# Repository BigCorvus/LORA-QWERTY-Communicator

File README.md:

# LORA-QWERTY-Communicator
A tidy, versatile and feature-packed LORA QWERTY communication device mainly based on a Blackberry Q10 keyboard, nRF52840, SX1262 and a 2.7'' Sharp Memory LCD (LS027B7DH01).
I created this because I wanted to practice a little and put some components that I had laying around to good use. The system had to have a low power consumption and outdoor usability, hence the component choices. The SX1262 draws 4,6mA in RX mode and the nRF52 can poll the keyboard while also drawing little power. Without optimizing anything I got 12mA. This can be further reduced by turning off some sensors. The unit can monitor its own power consumption and battery charge status via a BQ27441 Lithium Fuel Gauge.  

Some words about the memory LCDs: I got fake ones from Ali and only one out of three works properly! One consumes 20mA instead of ~400µA and one had some dead pixels after some days of usage (seen on the pictures). They are not that much cheaper (~25 vs ca 32$), so avoid them and only get genuine SHARP displays from digikey or so.  
There is a passive piezo buzzer (9032 type) and a vibration motor ("10x4mm" look on Aliexpress) for notification purposes. A BME280 can be soldered for altimeter functionality. A DS3231M RTC is supposed to keep time (the wires on the images are for optional backup battery connection). A MPU9250 9-DOF IMU was included to act as a tilt-compensated compass or for air mouse functionality. A GD25Q16CE QSPI flash (apparently optional, not required by the bootloader, works with mass storage TinyUSB test sketch) and an µSD card slot for storage of for example chat history or sensor values. An optional GPS module can be connected to the exposed connector at the top of the device. I used a BN220 which fits into the enclosure if you use an appropriate LiPo cell. All I2C sensor are on one I2C bus and are optional. They do not need to be populated. Time and altitude can just as well be fetched via GPS. The connector for the Q10 keyboard is a Hirose BM14B(0.8)-24DS-0.4V(53)     

The repository contains the EAGLE PCB design files, gerber, pick and place and BOM files, Solidworks design files and .STL for a perfectly fitting enclosure and an Arduino test sketch to test most of the system components. The enclosure lacks inserts for the pushbutton and slide swith. This I will add in the future. You require 4 2mmx10mm plastic screws to hold it together. The resulting device has a thickness of only about 13,5mm.  
While the hardware is confirmed working (only one minor bug had to be fixed in the prototype - conflicting I2C addresses), the firmware part is very raw and has yet to be developed. Unfortunately I lack time desperately for such hobby things at the moment. What I had in mind for this device is mainly something like an encrypted "apocalypse" LORA communicator, maybe even based on Meshtastic. It can also communicate with other BLE devices and acquire, log and share sensor data or act as a USB or BLE HID keyboard. The test firmware is based on the Adafruit nRF52 core v1.0.0. In order for the device to be programmable via the Arduino IDE, the Feather nRF52840 Express bootloader has to be flashed, which I usually do via a J-Link and the Arduino IDE ("Burn Bootloader"). The bootloader can be activated at any time double-pulling the reset pin low. In a future revision there should also be reset button for that purpose, now there is at least a test point. The variant files for the Feather nRF52840 express need to be modified as well before programming the board. They are provided with the test sketch together with a readme.  

UPDATE: Sam Altman and I created a nicely functioning Meshtastic port for this devices. The project is available as a zipped archive and as prebuilt-binaries.

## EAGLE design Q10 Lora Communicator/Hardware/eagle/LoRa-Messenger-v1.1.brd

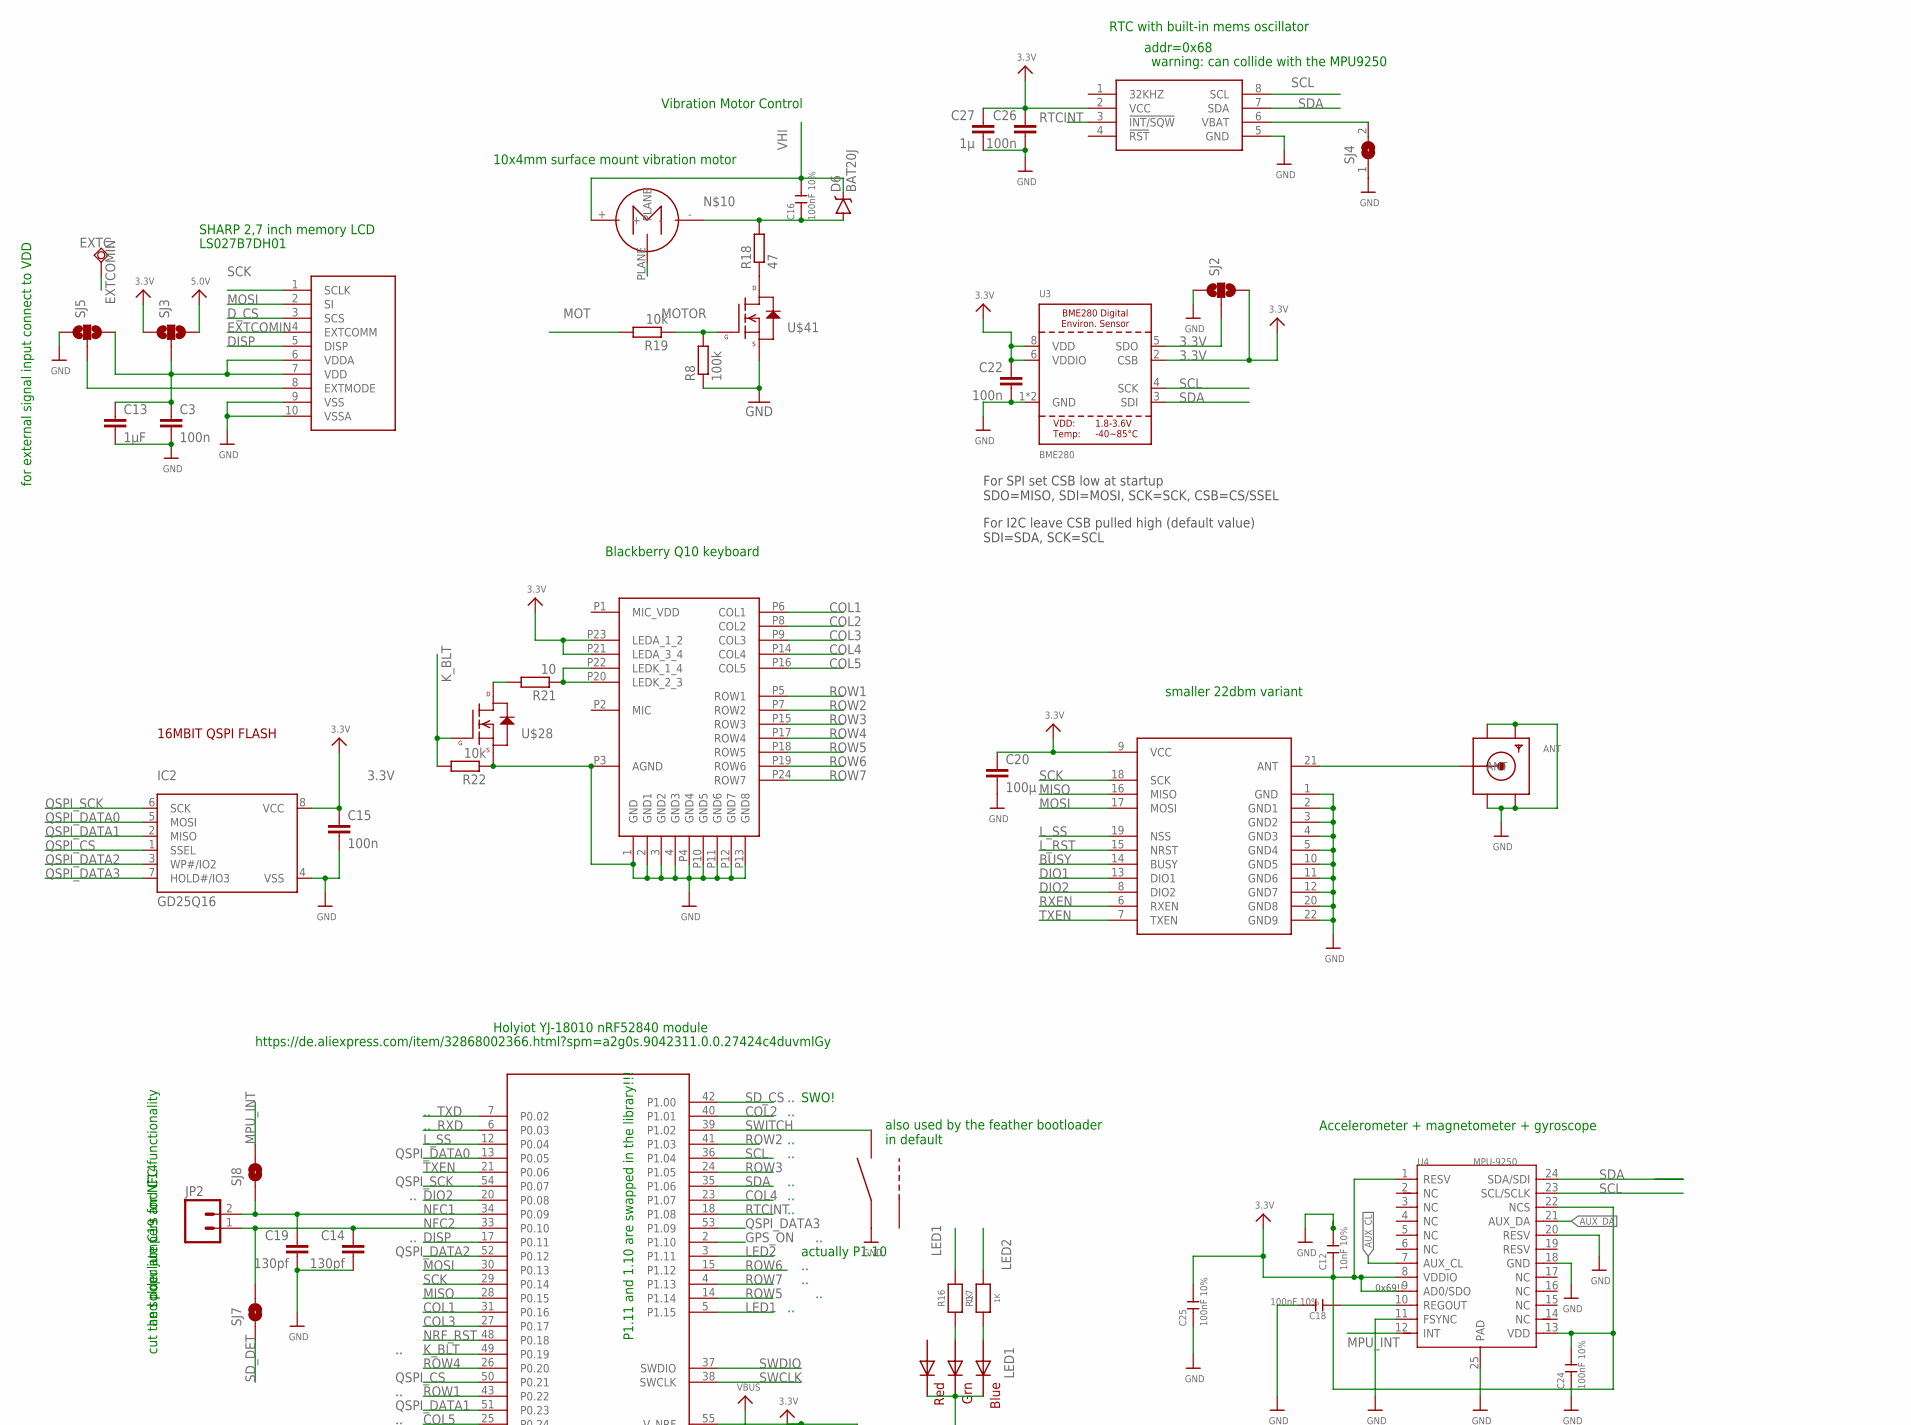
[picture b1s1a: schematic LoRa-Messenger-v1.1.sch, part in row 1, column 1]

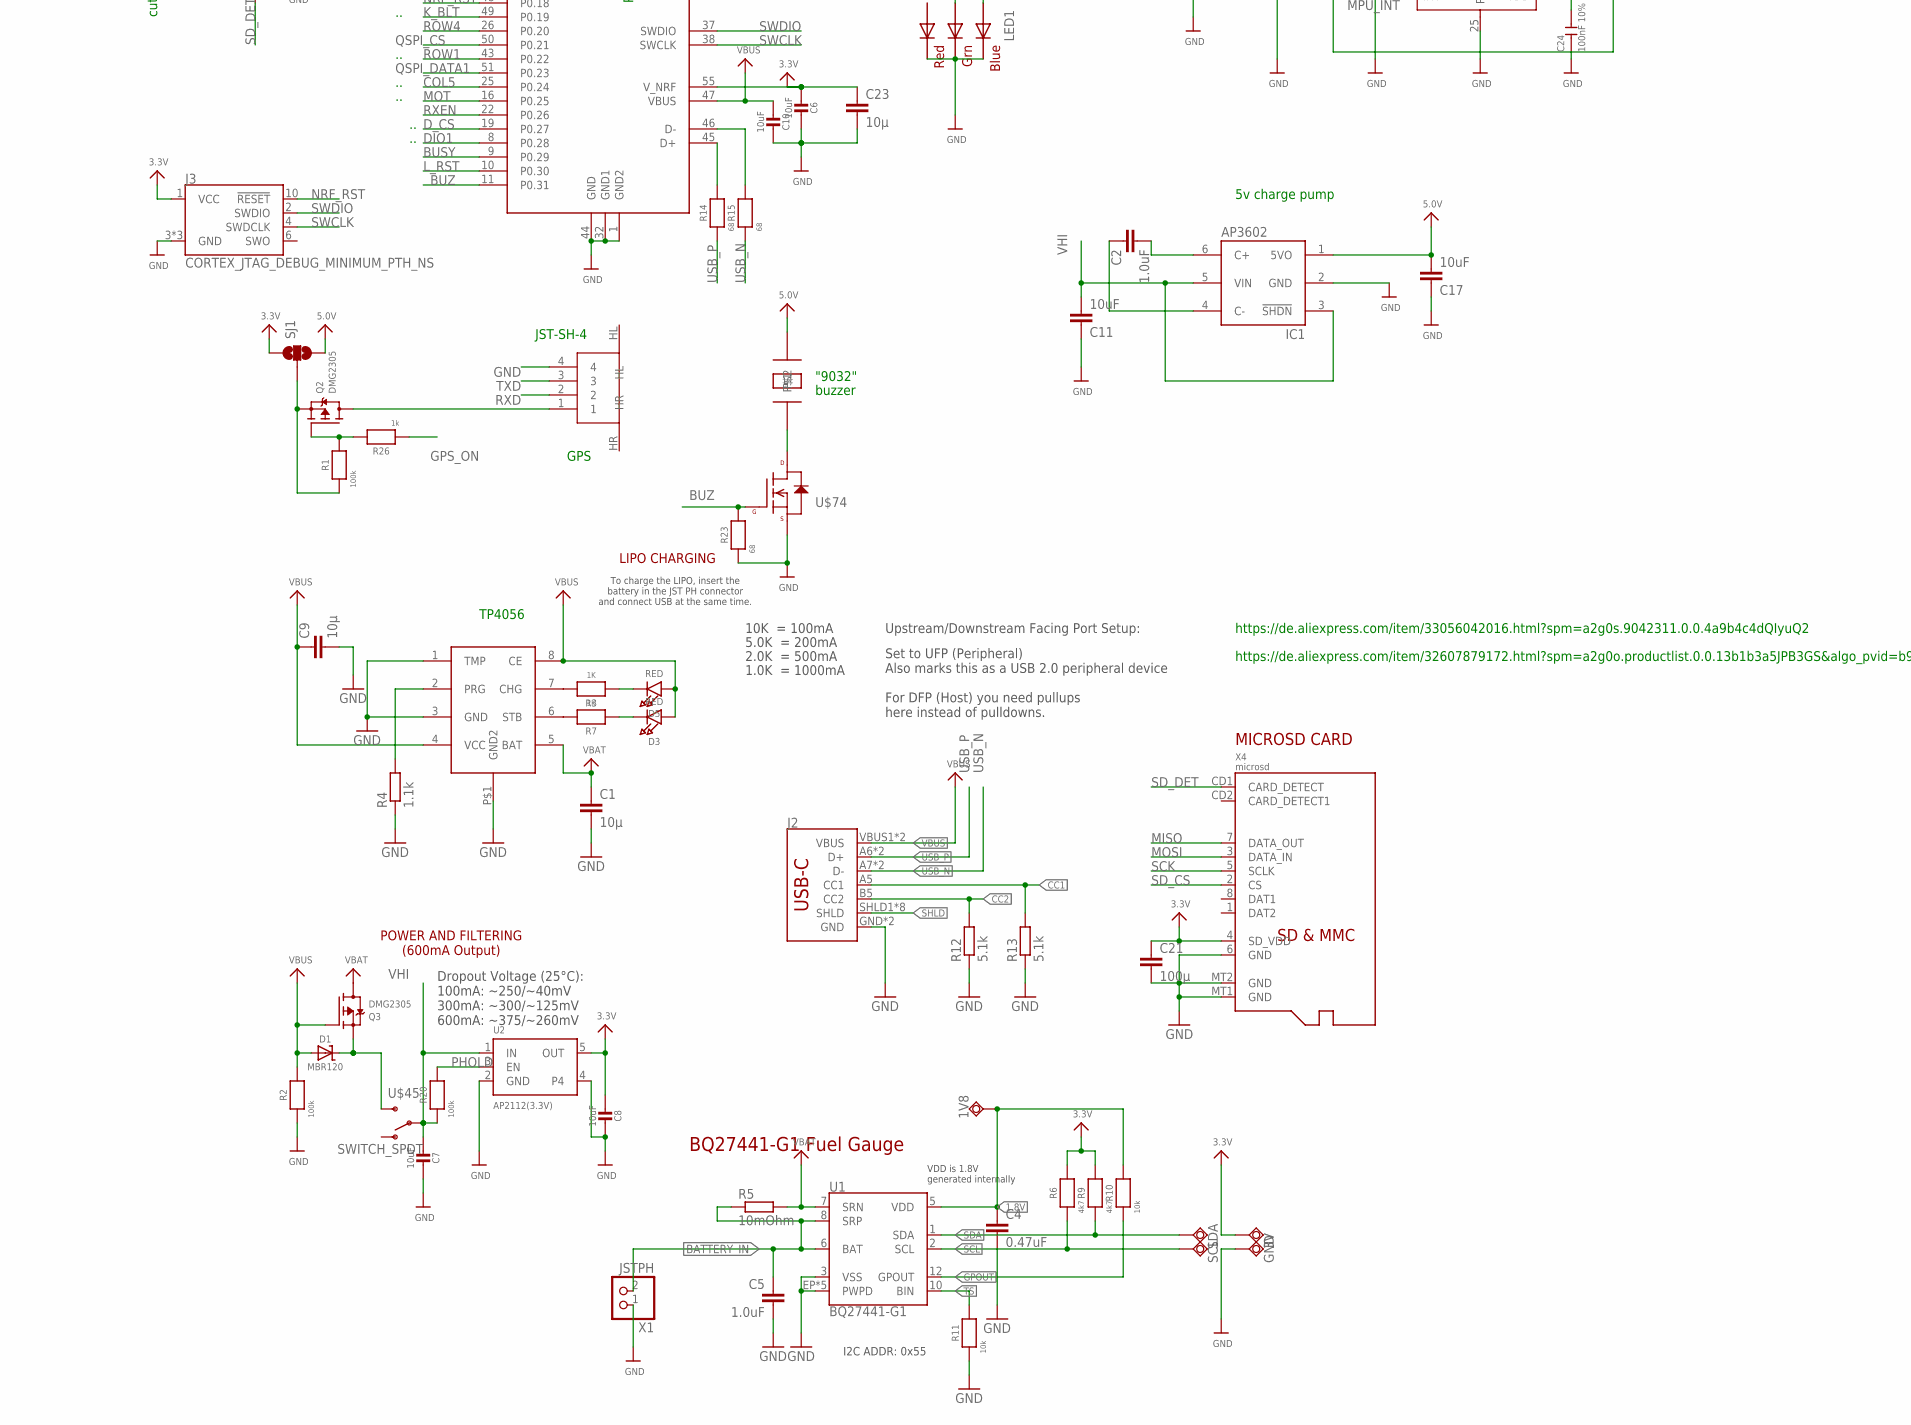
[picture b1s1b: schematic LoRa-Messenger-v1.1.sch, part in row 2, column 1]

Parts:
1V8, 3V: TPSQTP13R; TP13R
ANT: SMACONNECTOR_EDGE; SMA_EDGELAUNCH
C1, C9, C23: 10µ; C0805
C2, C5: 1.0uF; 0603-CAP
C3, C15: 100n; C0402
C4: 0.47uF; 0603-CAP
C6, C7, C8, C10: 10uF; 0805-NO
C11, C17: 10uF; 0603-CAP
C12: 10nF 10%; C0603
C13: 1µF; C0402
C14, C19: 130pf; 0603-CAP
C16, C18, C24, C25: 100nF 10%; C0603
C20, C21: 100µ; C1206
C22, C26: 100n; 0603-CAP
C27: 1µ; 0603-CAP
D1: MBR120; SOD-123
D3, D5: RED; CHIPLED_0805_NOOUTLINE
D6: BAT20J; SOD-323
DWN2: LS12T2
EXTC.: TPSQTP13R; TP13R
GND: TPSQTP13R; TP13R
IC1: AP3602; SOT23-6
IC2: GD25Q16; USON8
J2: USB_C16PIN; USB-C-16P
J3: CORTEX_JTAG_DEBUG_MINIMUM_PTH_NS; 2X5-PTH-1.27MM-NO_SILK
JP2: M02PTH; 1X02
LED1: RGBLED5050
Q2, Q3: DMG2305; SOT23-R
R1, R2, R20: 100k; 0603-NO
R3, R7, R16, R17: 1K; 0603-NO
R4: 1.1k; R0603
R5: 10mOhm; R0805
R6, R9: 4k7; 0603-NO
R8: 100k; R0603
R10, R11: 10k; 0603-NO
R12, R13: 5.1k; R0603
R14, R15, R23: 68; 0603-NO
R18: 47; R0603
R19, R22: 10k; R0603
R21: 10; R0603
R26: 1k; 0603-NO
SCL: TPSQTP13R; TP13R
SDA: TPSQTP13R; TP13R
SJ1, SJ2, SJ3, SJ5: SOLDERJUMPER_2WAY-OLDS; SJ_3
SJ4: SJ
SJ7, SJ8: SOLDERJUMPERTRACE; SJ_2S-TRACE
U1: BQ27441-G1; PDSO-N12
U2: AP2112(3.3V); SOT23-5
U3: BME280
U4: MPU-9250; LEAD-QFN24
U$2: BUZZER
U$7: Q10KEYBOARD
U$10: AYF531035_SHARP_MEM_DISP; AYF531035_Y5BW
U$14: NRF52840; NRF52840MOD
U$17: JST-SH-3
U$28, U$41, U$74: N-CHANNEL-MOSFET-BSS138; SOT23-3
U$36: SX1292-EBYTE; SX1262_EBYTE
U$45: SWITCH_SPDT; KPS-1290
U$46: VIBRO
U$47: TP4056BETTER_TP4056; TP4056BETTER_SO-08
U$69: DS3231M; SO8
X1: JSTPH; JSTPH2
X4: microsd; MICROSD

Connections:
1.8V: 1V8.TP, C4.1, R10.2, U1.5 (VDD)
3.3V: 3V.TP, C6.2, C8.2, C12.1, C15.1, C20.1, C21.1, C22.1, C23.1, C24.2, C25.2, C26.1, C27.1, IC2.8 (VCC), J3.1 (VCC), R6.2, R9.2, SJ1.1, SJ2.3, SJ3.1, U2.5 (OUT), U3.2 (CSB), U3.6 (VDDIO), U3.8 (VDD), U4.1 (RESV), U4.8 (VDDIO), U4.9 (AD0/SDO), U4.13 (VDD), U4.22 (NCS), U$7.P21 (LEDA_3_4), U$7.P23 (LEDA_1_2), U$14.55 (V_NRF), U$36.9 (VCC), U$69.2 (VCC), X4.4 (SD_VDD)
5.0V: C17.2, IC1.1 (5VO), SJ1.3, SJ3.3, U$2.P$1
AUX_CL: U4.7 (AUX_CL)
AUX_DA: U4.21 (AUX_DA)
BATTERY_IN: C5.1, R5.1, U1.6 (BAT), U1.8 (SRP), X1.2
BUSY: U$14.9 (P0.29), U$36.14 (BUSY)
BUZ: R23.2, U$14.11 (P0.31), U$74.1 (G)
CC1: J2.A5 (CC1), R13.2
CC2: J2.B5 (CC2), R12.2
COL1: U$7.P6 (COL1), U$14.31 (P0.16)
COL2: U$7.P8 (COL2), U$14.40 (P1.01)
COL3: U$7.P9 (COL3), U$14.27 (P0.17)
COL4: U$7.P14 (COL4), U$14.23 (P1.07)
COL5: U$7.P16 (COL5), U$14.25 (P0.24)
DIO1: U$14.8 (P0.28), U$36.13 (DIO1)
DIO2: U$14.20 (P0.08), U$36.8 (DIO2)
DISP: U$10.5 (DISP), U$14.17 (P0.11)
D_CS: U$10.3 (SCS), U$14.19 (P0.27)
EXTCOMIN: EXTC..TP, U$10.4 (EXTCOMM)
GND: ANT.GND@1 (GND4), ANT.GND@2 (GND3), ANT.GND@3 (GND2), ANT.GND@4 (GND1), C1.2, C3.2, C4.2, C5.2, C6.1, C7.1, C8.1, C9.2, C10.1, C11.1, C12.2, C13.2, C14.2, C15.2, C17.1, C18.2, C19.2, C20.2, C21.2, C22.2, C23.2, C24.1, C25.1, C26.2, C27.2, DWN2.2, GND.TP, IC1.2 (GND), IC2.4 (VSS), J2.GND, J2.GND2 (GND), J3.3 (GND), J3.5 (GND), J3.9 (GND), LED1.4 (BLUE_C), LED1.5 (RED_C), LED1.6 (GREEN_C), R2.1, R4.1, R8.1, R11.1, R12.1, R13.1, R22.1, R23.1, SJ2.1, SJ4.1, SJ5.1, U1.3 (VSS), U1.EP (PWPD), U1.EP1 (PWPD), U1.EP2 (PWPD), U1.EP3 (PWPD), U1.EP4 (PWPD), U2.2 (GND), U2.4, U3.1 (GND), U3.7 (GND), U4.11 (FSYNC), U4.18 (GND), U4.20 (RESV), U4.25 (PAD), U$7.1 (GND), U$7.2 (GND1), U$7.3 (GND2), U$7.4 (GND3), U$7.P3 (AGND), U$7.P4 (GND4), U$7.P10 (GND5), U$7.P11 (GND6), U$7.P12 (GND7), U$7.P13 (GND8), U$10.9 (VSS), U$10.10 (VSSA), U$14.1 (GND2), U$14.32 (GND1), U$14.44 (GND), U$17.4, U$28.2 (S), U$36.1 (GND), U$36.2 (GND1), U$36.3 (GND2), U$36.4 (GND3), U$36.5 (GND4), U$36.10 (GND5), U$36.11 (GND6), U$36.12 (GND7), U$36.20 (GND8), U$36.22 (GND9), U$41.2 (S), U$47.1 (TMP), U$47.3 (GND), U$47.P$1 (GND2), U$69.5 (GND), U$74.2 (S), X1.1, X4.6 (GND), X4.MT1 (GND), X4.MT2 (GND)
GPOUT: R10.1, U1.12 (GPOUT)
GPS_ON: R26.1, U$14.2 (P1.10)
K_BLT: R22.2, U$14.49 (P0.19), U$28.1 (G)
LED1: R16.2, U$14.5 (P1.15)
LED2: R17.2, U$14.3 (P1.11)
L_RST: U$14.10 (P0.30), U$36.15 (NRST)
L_SS: U$14.12 (P0.04), U$36.19 (NSS)
MISO: U$14.28 (P0.15), U$36.16 (MISO), X4.7 (DATA_OUT)
MOSI: U$10.2 (SI), U$14.30 (P0.13), U$36.17 (MOSI), X4.3 (DATA_IN)
MOT: R19.2, U$14.16 (P0.25)
MOTOR: R8.2, R19.1, U$41.1 (G)
MPU_INT: SJ8.2, U4.12 (INT)
unnamed: R3.2, U$47.7 (CHG)
unnamed: C2.2, IC1.6 (C+)
unnamed: C2.1, IC1.4 (C-)
unnamed: D1.C, Q3.2 (S), U$45.S
unnamed: Q2.1 (G), R1.2, R26.2
unnamed: R14.2, U$14.45 (D+)
unnamed: R15.2, U$14.46 (D-)
unnamed: R7.2, U$47.6 (STB)
unnamed: R18.1, U$41.3 (D)
unnamed: C16.1, D6.A, R18.2, U$46.-
unnamed: D5.C, R3.1
unnamed: D3.C, R7.1
unnamed: LED1.1 (GREEN_A), R16.1
unnamed: Q2.3 (D), U$17.1
unnamed: R21.1, U$7.P20 (LEDK_2_3), U$7.P22 (LEDK_1_4)
unnamed: Q2.2 (S), R1.1, SJ1.2
unnamed: R21.2, U$28.3 (D)
unnamed: ANT.P (ANT), U$36.21 (ANT)
unnamed: LED1.3 (BLUE_A), R17.1
unnamed: SJ2.2, U3.5 (SDO)
unnamed: U$2.P$2, U$74.3 (D)
unnamed: C18.1, U4.10 (REGOUT)
unnamed: SJ4.2, U$69.6 (VBAT)
unnamed: C3.1, C13.1, SJ3.2, SJ5.3, U$10.6 (VDDA), U$10.7 (VDD)
unnamed: SJ5.2, U$10.8 (EXTMODE)
NFC1: C19.1, JP2.2, SJ8.1, U$14.34 (P0.09)
NFC2: C14.1, JP2.1, SJ7.2, U$14.33 (P0.10)
NRF_RST: J3.10 (!RESET), U$14.48 (P0.18)
PHOLD: R20.2, U2.3 (EN)
PLANE: U$46.PLANE
PRG: R4.2, U$47.2 (PRG)
QSPI_CS: IC2.1 (SSEL), U$14.50 (P0.21)
QSPI_DATA0: IC2.5 (MOSI), U$14.13 (P0.05)
QSPI_DATA1: IC2.2 (MISO), U$14.51 (P0.23)
QSPI_DATA2: IC2.3 (WP#/IO2), U$14.52 (P0.12)
QSPI_DATA3: IC2.7 (HOLD#/IO3), U$14.53 (P1.09)
QSPI_SCK: IC2.6 (SCK), U$14.54 (P0.07)
ROW1: U$7.P5 (ROW1), U$14.43 (P0.22)
ROW2: U$7.P7 (ROW2), U$14.41 (P1.03)
ROW3: U$7.P15 (ROW3), U$14.24 (P1.05)
ROW4: U$7.P17 (ROW4), U$14.26 (P0.20)
ROW5: U$7.P18 (ROW5), U$14.14 (P1.14)
ROW6: U$7.P19 (ROW6), U$14.15 (P1.12)
ROW7: U$7.P24 (ROW7), U$14.4 (P1.13)
RTCINT: U$14.18 (P1.08), U$69.3 (!INT/SQW)
RXD: U$14.6 (P0.03), U$17.2
RXEN: U$14.22 (P0.26), U$36.6 (RXEN)
SCK: U$10.1 (SCLK), U$14.29 (P0.14), U$36.18 (SCK), X4.5 (SCLK)
SCL: R6.1, SCL.TP, U1.2 (SCL), U3.4 (SCK), U4.23 (SCL/SCLK), U$14.36 (P1.04), U$69.8 (SCL)
SDA: R9.1, SDA.TP, U1.1 (SDA), U3.3 (SDI), U4.24 (SDA/SDI), U$14.35 (P1.06), U$69.7 (SDA)
SD_CS: U$14.42 (P1.00), X4.2 (CS)
SD_DET: SJ7.1, X4.CD1 (CARD_DETECT)
SHLD: J2.SHLD1 (SHLD), J2.SHLD2 (SHLD), J2.SHLD3 (SHLD), J2.SHLD4 (SHLD), J2.SHLD5 (SHLD), J2.SHLD6 (SHLD), J2.SHLD7 (SHLD), J2.SHLD8 (SHLD)
SWCLK: J3.4 (SWDCLK), U$14.38 (SWCLK)
SWDIO: J3.2 (SWDIO), U$14.37 (SWDIO)
SWITCH: DWN2.1, U$14.39 (P1.02)
TS: R11.2, U1.10 (BIN)
TXD: U$14.7 (P0.02), U$17.3
TXEN: U$14.21 (P0.06), U$36.7 (TXEN)
USB_N: J2.A7 (D-), J2.B7 (D-), R15.1
USB_P: J2.A6 (D+), J2.B6 (D+), R14.1
VBAT: C1.1, Q3.3 (D), R5.2, U1.7 (SRN), U$47.5 (BAT)
VBUS: C9.1, C10.2, D1.A, D3.A, D5.A, J2.VBUS1 (VBUS), J2.VBUS2 (VBUS), Q3.1 (G), R2.2, U$14.47 (VBUS), U$47.4 (VCC), U$47.8 (CE)
VHI: C7.2, C11.2, C16.2, D6.C, IC1.3 (!SHDN), IC1.5 (VIN), R20.1, U2.1 (IN), U$45.P, U$46.+

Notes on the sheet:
POWER AND FILTERING (600mA Output)
Dropout Voltage (25°C): 100mA: ~250/~40mV 300mA: ~300/~125mV 600mA: ~375/~260mV
10K = 100mA
5.0K = 200mA
2.0K = 500mA
1.0K = 1000mA
LIPO CHARGING
To charge the LIPO, insert the battery in the JST PH connector and connect USB at the same time.
BQ27441-G1 Fuel Gauge
VDD is 1.8V generated internally
I2C ADDR: 0x55
Holyiot YJ-18010 nRF52840 module
P1.11 and 1.10 are swapped in the library!!!
GPS
MICROSD CARD
Set to UFP (Peripheral) Also marks this as a USB 2.0 peripheral device For DFP (Host) you need pullups here instead of pulldowns.
Upstream/Downstream Facing Port Setup:
JST-SH-4
TP4056
smaller 22dbm variant
also used by the feather bootloader in default
For SPI set CSB low at startup SDO=MISO, SDI=MOSI, SCK=SCK, CSB=CS/SSEL
For I2C leave CSB pulled high (default value) SDI=SDA, SCK=SCL
actually P1.10
https://de.aliexpress.com/item/33056042016.html?spm=a2g0s.9042311.0.0.4a9b4c4dQIyuQ2
https://de.aliexpress.com/item/32868002366.html?spm=a2g0s.9042311.0.0.27424c4duvmlGy
https://de.aliexpress.com/item/32607879172.html?spm=a2g0o.productlist.0.0.13b1b3a5JPB3GS&algo_pvid=b9191f80-57f7-4ba1-a376-d5b7fd01a70f&algo_expid=b9191f80-57f7-4ba1-a376-d5b7fd01a70f-25&btsid=0ab50f4915950751178702682eb47a&ws_ab_test=searchweb0_0,searchweb201602_,searchweb201603_
16MBIT QSPI FLASH
for external signal input connect to VDD
Vibration Motor Control
0x69!!
Accelerometer + magnetometer + gyroscope
RTC with built-in mems oscillator
SWO!
cut the solder jumpers for NFC functionality
and populate C19 and C14
Blackberry Q10 keyboard
SHARP 2,7 inch memory LCD
addr=0x68
5v charge pump

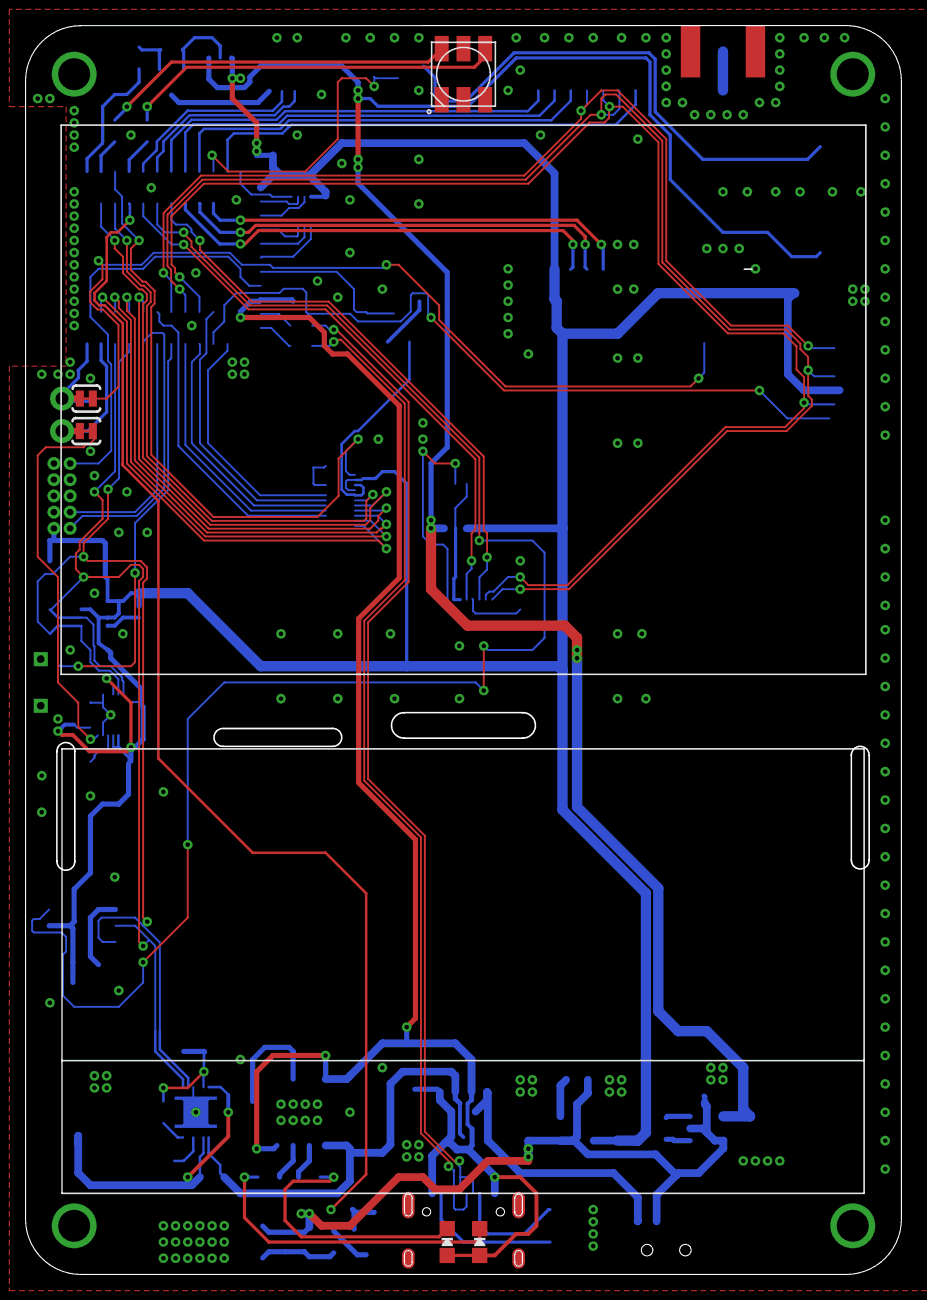
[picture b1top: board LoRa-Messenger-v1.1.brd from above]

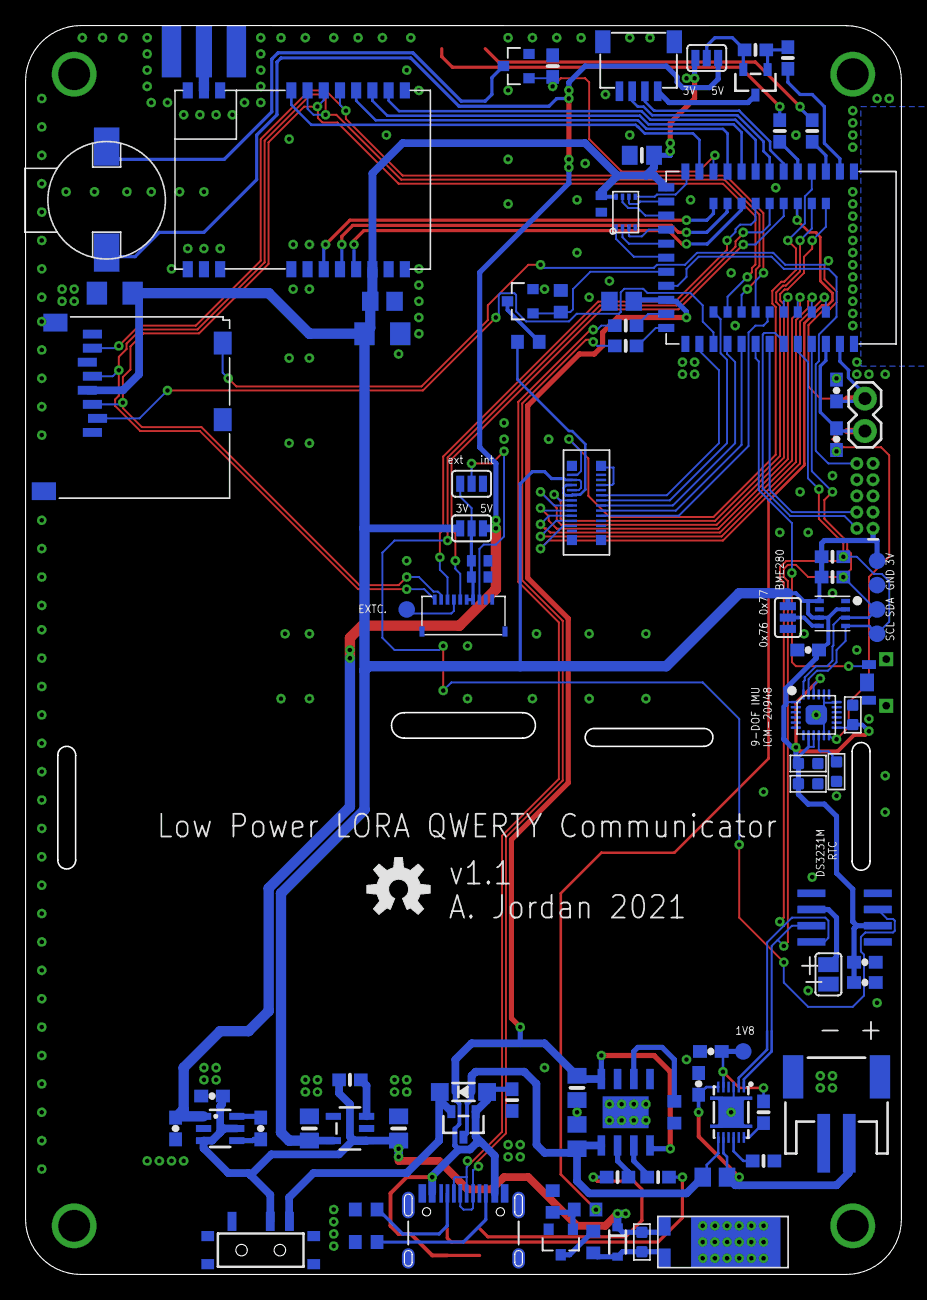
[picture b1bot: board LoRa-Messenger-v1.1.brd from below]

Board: 2 copper layers, 68.6 x 97.8 mm, 98 parts (91 on the bottom side), 94 nets.

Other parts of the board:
U$77: OSHW-LOGO-M

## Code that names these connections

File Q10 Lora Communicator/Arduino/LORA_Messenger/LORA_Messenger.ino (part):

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//#define SPI_MOSI         13
//#define SPI_SCK          14
//Q10 keyboard defines
#define col1    16
#define col2    33
#define col3    17
#define col4    39
#define col5    24

#define row1    22
#define row2    35
#define row3    37
#define row4    20
#define row5    46
#define row6    44
#define row7    45
//PIN defines
#define IMU_INT       9
#define RTC_INT       40
#define PIN_BUZZER    31
#define GPS_ON        43 //LOW means on
#define MOT           25 //HIGH means ON
#define K_BLT         19 //HIGH means ON
#define DISP_CS       27
#define DISP_DISP     11
#define BTN           34 
#define SD_CS         32
#define SD_DET        10

#define DIO1 (28)
#define DIO2 (8)
#define TXEN (6)
#define RXEN (26)
#define L_SS (4)
#define BUSY (29)
#define L_RST (30)

//-------------------menue variables-------------------
//in order to add a new app you have to:
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
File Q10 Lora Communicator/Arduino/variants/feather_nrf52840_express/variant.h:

 /*
  Copyright (c) 2014-2015 Arduino LLC.  All right reserved.
  Copyright (c) 2016 Sandeep Mistry All right reserved.
  Copyright (c) 2018, Adafruit Industries (adafruit.com)

  This library is free software; you can redistribute it and/or
  modify it under the terms of the GNU Lesser General Public
  License as published by the Free Software Foundation; either
  version 2.1 of the License, or (at your option) any later version.
  This library is distributed in the hope that it will be useful,
  but WITHOUT ANY WARRANTY; without even the implied warranty of
  MERCHANTABILITY or FITNESS FOR A PARTICULAR PURPOSE.
  See the GNU Lesser General Public License for more details.
  You should have received a copy of the GNU Lesser General Public
  License along with this library; if not, write to the Free Software
  Foundation, Inc., 51 Franklin St, Fifth Floor, Boston, MA  02110-1301  USA
*/

#ifndef _VARIANT_FEATHER52840_
#define _VARIANT_FEATHER52840_

/** Master clock frequency */
#define VARIANT_MCK       (64000000ul)

#define USE_LFXO      // Board uses 32khz crystal for LF
// define USE_LFRC    // Board uses RC for LF

/*----------------------------------------------------------------------------
 *        Headers
 *----------------------------------------------------------------------------*/

#include "WVariant.h"

#ifdef __cplusplus
extern "C"
{
#endif // __cplusplus


// Number of pins defined in PinDescription array
#define PINS_COUNT           (48)
#define NUM_DIGITAL_PINS     (48)
#define NUM_ANALOG_INPUTS    (6) // A6 is used for battery, A7 is analog reference
#define NUM_ANALOG_OUTPUTS   (0)

// LEDs
#define PIN_LED1             (42)
#define PIN_LED2             (47)
#define PIN_NEOPIXEL         (8)
#define NEOPIXEL_NUM         1

#define LED_BUILTIN          PIN_LED1
#define LED_CONN             PIN_LED2

#define LED_RED              PIN_LED1
#define LED_BLUE             PIN_LED2

#define LED_STATE_ON         1         // State when LED is litted

/*
 * Buttons
 */
#define PIN_BUTTON1          (34)

/*
 * Analog pins
 */
#define PIN_A0               (14)
#define PIN_A1               (15)
#define PIN_A2               (16)
#define PIN_A3               (17)
#define PIN_A4               (18)
#define PIN_A5               (19)
#define PIN_A6               (20)
#define PIN_A7               (21)

static const uint8_t A0  = PIN_A0 ;
static const uint8_t A1  = PIN_A1 ;
static const uint8_t A2  = PIN_A2 ;
static const uint8_t A3  = PIN_A3 ;
static const uint8_t A4  = PIN_A4 ;
static const uint8_t A5  = PIN_A5 ;
static const uint8_t A6  = PIN_A6 ;
static const uint8_t A7  = PIN_A7 ;
#define ADC_RESOLUTION    14

// Other pins
#define PIN_AREF           PIN_A7
#define PIN_VBAT           PIN_A6
#define PIN_NFC1           (9)
#define PIN_NFC2           (10)

static const uint8_t AREF = PIN_AREF;

/*
 * Serial interfaces
 */
#define PIN_SERIAL1_RX       (3)
#define PIN_SERIAL1_TX       (2)

/*
 * SPI Interfaces
 */
#define SPI_INTERFACES_COUNT 1

#define PIN_SPI_MISO         (15)
#define PIN_SPI_MOSI         (13)
#define PIN_SPI_SCK          (14)

static const uint8_t SS   = (27);
static const uint8_t MOSI = PIN_SPI_MOSI ;
static const uint8_t MISO = PIN_SPI_MISO ;
static const uint8_t SCK  = PIN_SPI_SCK ;

/*
 * Wire Interfaces
 */
#define WIRE_INTERFACES_COUNT 1

#define PIN_WIRE_SDA         (38)
#define PIN_WIRE_SCL         (36)

// QSPI Pins
#define PIN_QSPI_SCK         7
#define PIN_QSPI_CS          21
#define PIN_QSPI_IO0         5
#define PIN_QSPI_IO1         23
#define PIN_QSPI_IO2         12
#define PIN_QSPI_IO3         41



// On-board QSPI Flash
#define EXTERNAL_FLASH_DEVICES   GD25Q16C
#define EXTERNAL_FLASH_USE_QSPI

#ifdef __cplusplus
}
#endif

/*----------------------------------------------------------------------------
 *        Arduino objects - C++ only
 *----------------------------------------------------------------------------*/

#endif

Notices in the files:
parts and their libraries:
microbuilder: This work is placed in the public domain, and may be freely used for commercial and non-commercial work with the following conditions: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
SparkFun-Capacitors: Licensing: Creative Commons ShareAlike 4.0 International - https://creativecommons.org/licenses/by-sa/4.0
